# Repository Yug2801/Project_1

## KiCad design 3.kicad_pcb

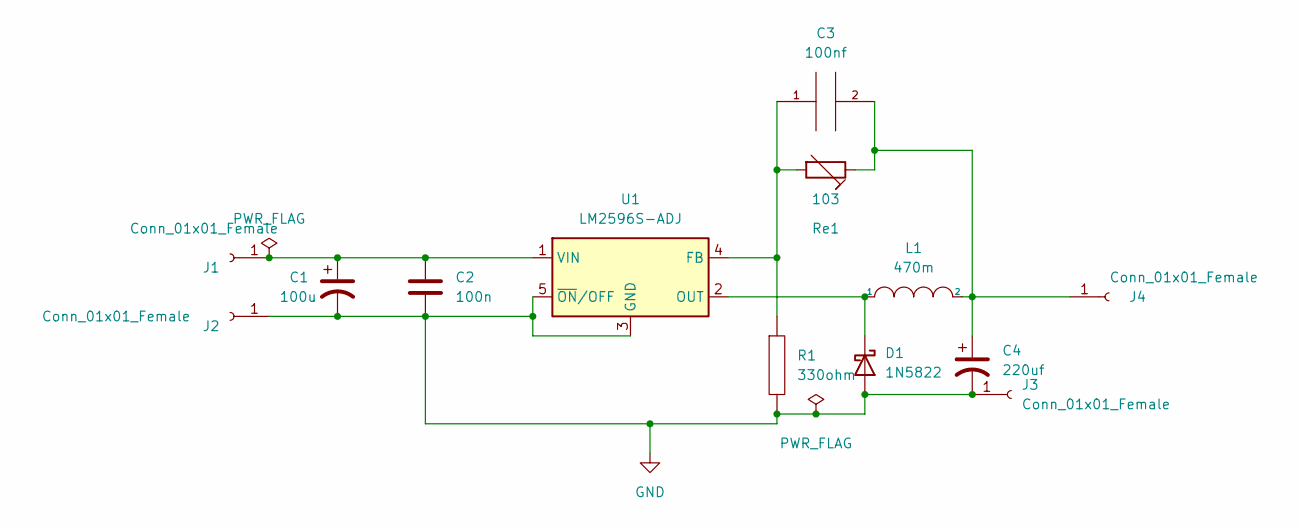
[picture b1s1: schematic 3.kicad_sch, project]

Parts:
C1: 100u; CP_Elec_3x5.3
C2: 100n; CP_Elec_3x5.3
C3: 100nf; CP_Elec_3x5.3
C4: 220uf; CP_Elec_3x5.3
D1: 1N5822; D_DO-201AD_P15.24mm_Horizontal
J1, J2, J3, J4: Conn_01x01_Female; Banana_Jack_1Pin
L1: 470m; L_6.3x6.3_H3
R1: 330ohm; R_0201_0603Metric
Re1: 103; OnSemi_CASE100AQ
U1: LM2596S-ADJ; TO-263-5_TabPin3

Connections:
GND: C1.2, C2.2, C4.2, D1.2 (A), J2.1, J3.1, R1.2, U1.3 (GND), U1.5 (~ON/OFF)
unnamed: C1.1, C2.1, J1.1, U1.1 (VIN)
unnamed: D1.1 (K), L1.1, U1.2 (OUT)
unnamed: C3.2, C4.1, J4.1, L1.2, Re1.1
unnamed: C3.1, R1.1, Re1.2, U1.4 (FB)

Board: 2 copper layers, 13 parts (0 on the bottom side), 5 nets, no tracks yet.

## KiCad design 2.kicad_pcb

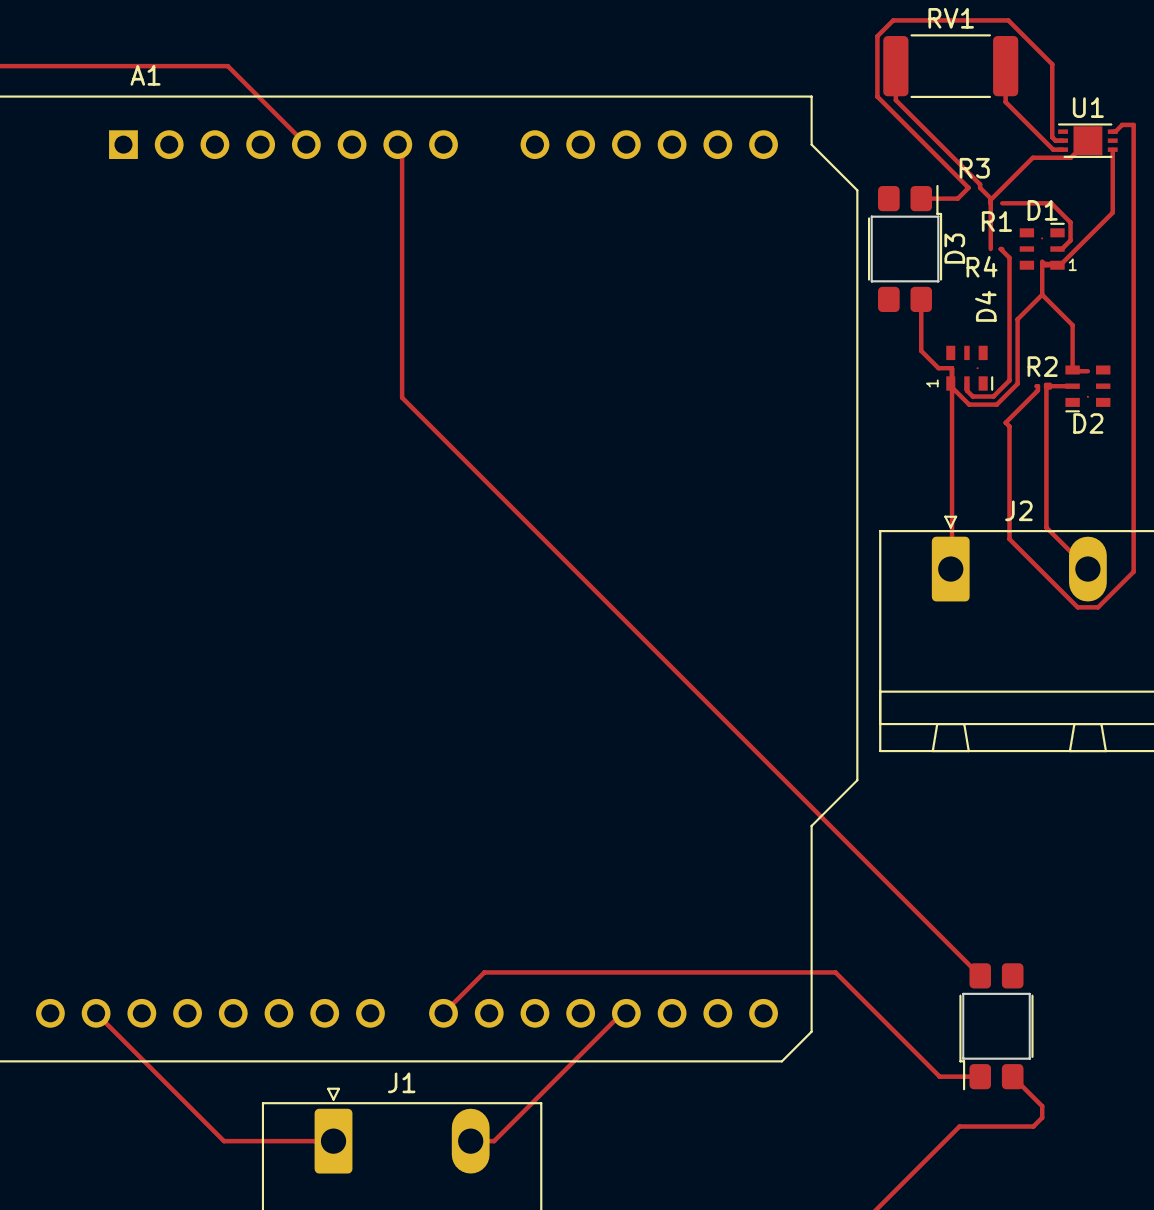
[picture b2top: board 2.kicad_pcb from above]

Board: 2 copper layers, 14 parts (0 on the bottom side), 13 nets.

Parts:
A1: Arduino_UNO_R2
D1, D2, D4: LED; LED-APA102-2020
D3: D_Photo; Everlight_ITR8307
J1: Conn_01x03_Female; PhoenixContact_GMSTBA_2,5_2-G-7,62_1x02_P7.62mm_Horizontal
J2: Conn_01x03_Male; PhoenixContact_GMSTBA_2,5_2-G-7,62_1x02_P7.62mm_Horizontal
M1: Motor_Servo_AirTronics; Everlight_ITR8307
R1, R2, R3, R4: R; R_0201_0603Metric
RV1: R_Potentiometer; R_2512_6332Metric_Pad1.40x3.35mm_HandSolder
U1: LM741; HVSOF6

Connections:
unnamed: A1.5 (+5V), M1.3 (PWM)
unnamed: A1.7 (GND), M1.2 (-)
unnamed: A1.18 (D3), J1.2
unnamed: A1.22 (D7), M1.1 (+)
unnamed: A1.29 (GND), J1.1
unnamed: D1.1 (K), D2.1 (K), D3.2 (A), D4.1 (K), J2.1, U1.4 (V-)
unnamed: D1.2 (A), R1.1
unnamed: D2.2 (A), J2.2, R2.2
unnamed: D3.1 (K), R3.1, U1.2 (-)
unnamed: D4.2 (A), R4.1
unnamed: R1.2, R3.2, R4.2, RV1.1, U1.7 (V+)
unnamed: R2.1, U1.6
unnamed: RV1.2, U1.3 (+)

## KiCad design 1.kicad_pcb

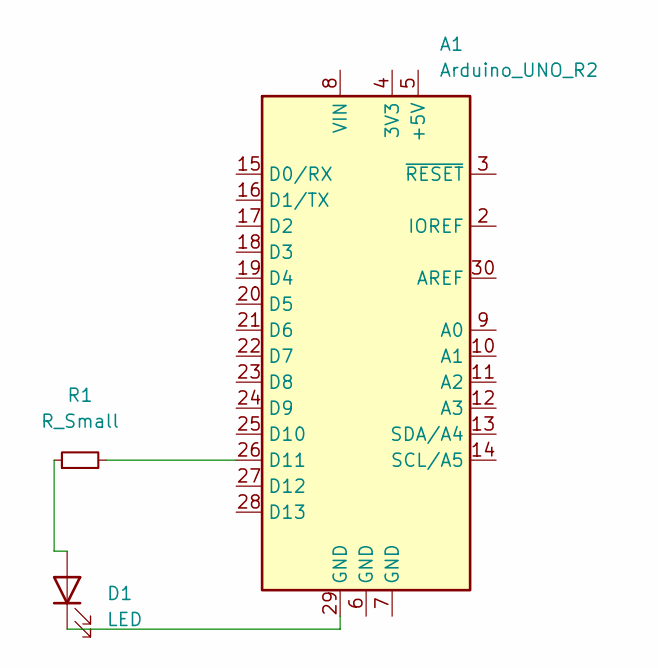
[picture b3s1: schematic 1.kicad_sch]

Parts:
A1: Arduino_UNO_R2
D1: LED; LED_0201_0603Metric
R1: R_Small; R_0201_0603Metric

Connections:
unnamed: A1.26 (D11), R1.2
unnamed: A1.29 (GND), D1.1 (K)
unnamed: D1.2 (A), R1.1

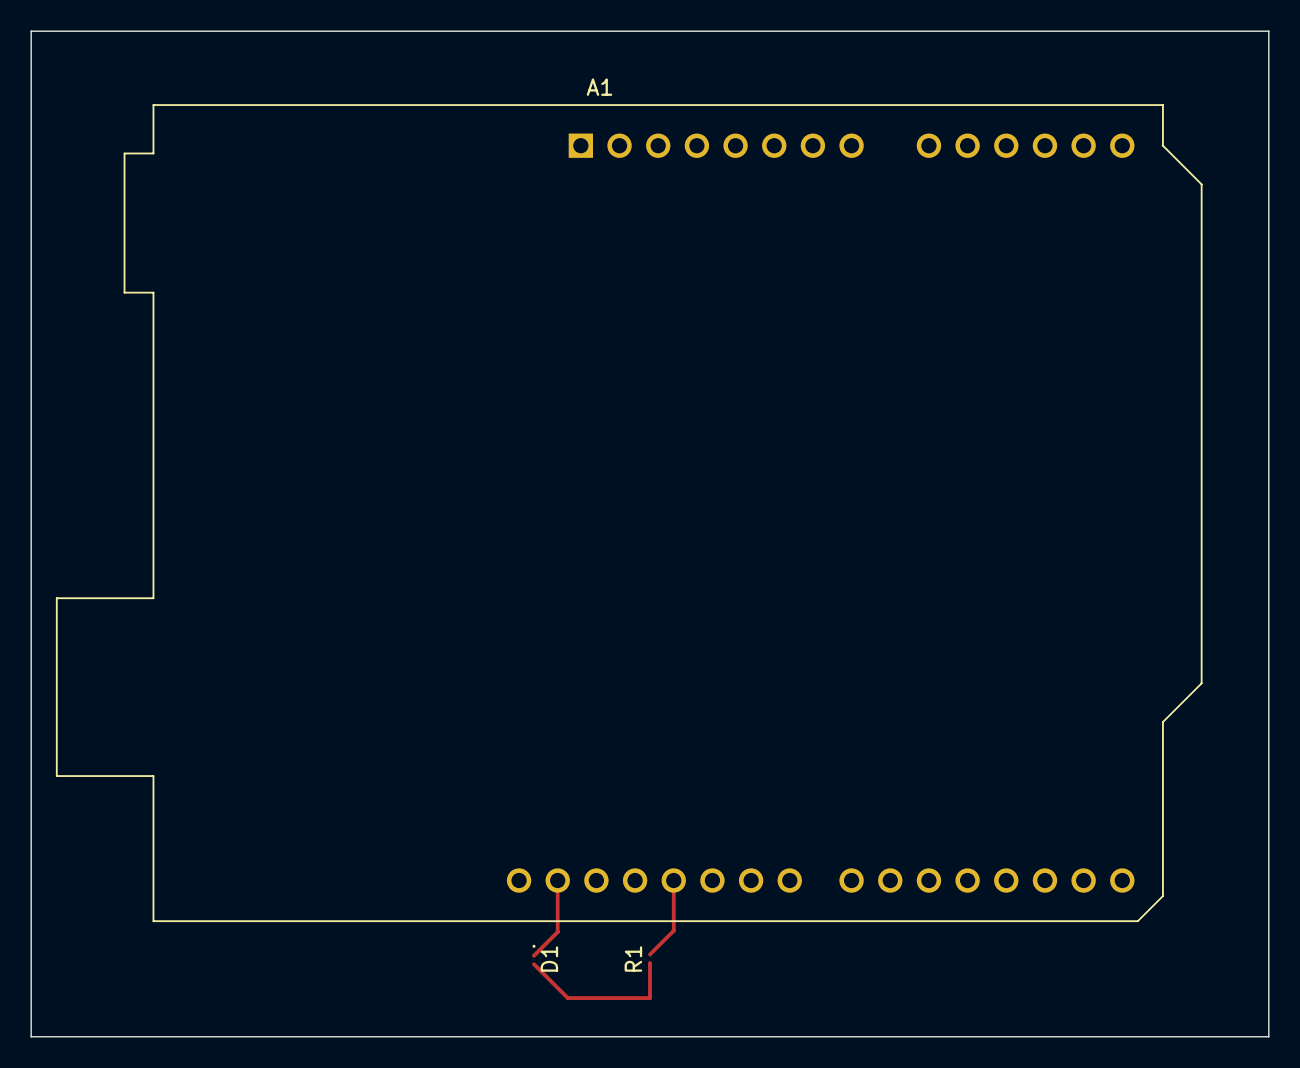
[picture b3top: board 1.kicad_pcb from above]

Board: 2 copper layers, 81.3 x 66.0 mm, 3 parts (0 on the bottom side), 3 nets.

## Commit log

2022-06-09 Create LED
2022-06-09 Create servo motor using a potentiometer
2022-06-09 Create 3..a Controlling LED intensity using PWM registers directly
2022-06-09 Create 3.b Sweep a servo without using the Servo library controlled with IR remote.
2022-06-12 Update servo motor using a potentiometer
